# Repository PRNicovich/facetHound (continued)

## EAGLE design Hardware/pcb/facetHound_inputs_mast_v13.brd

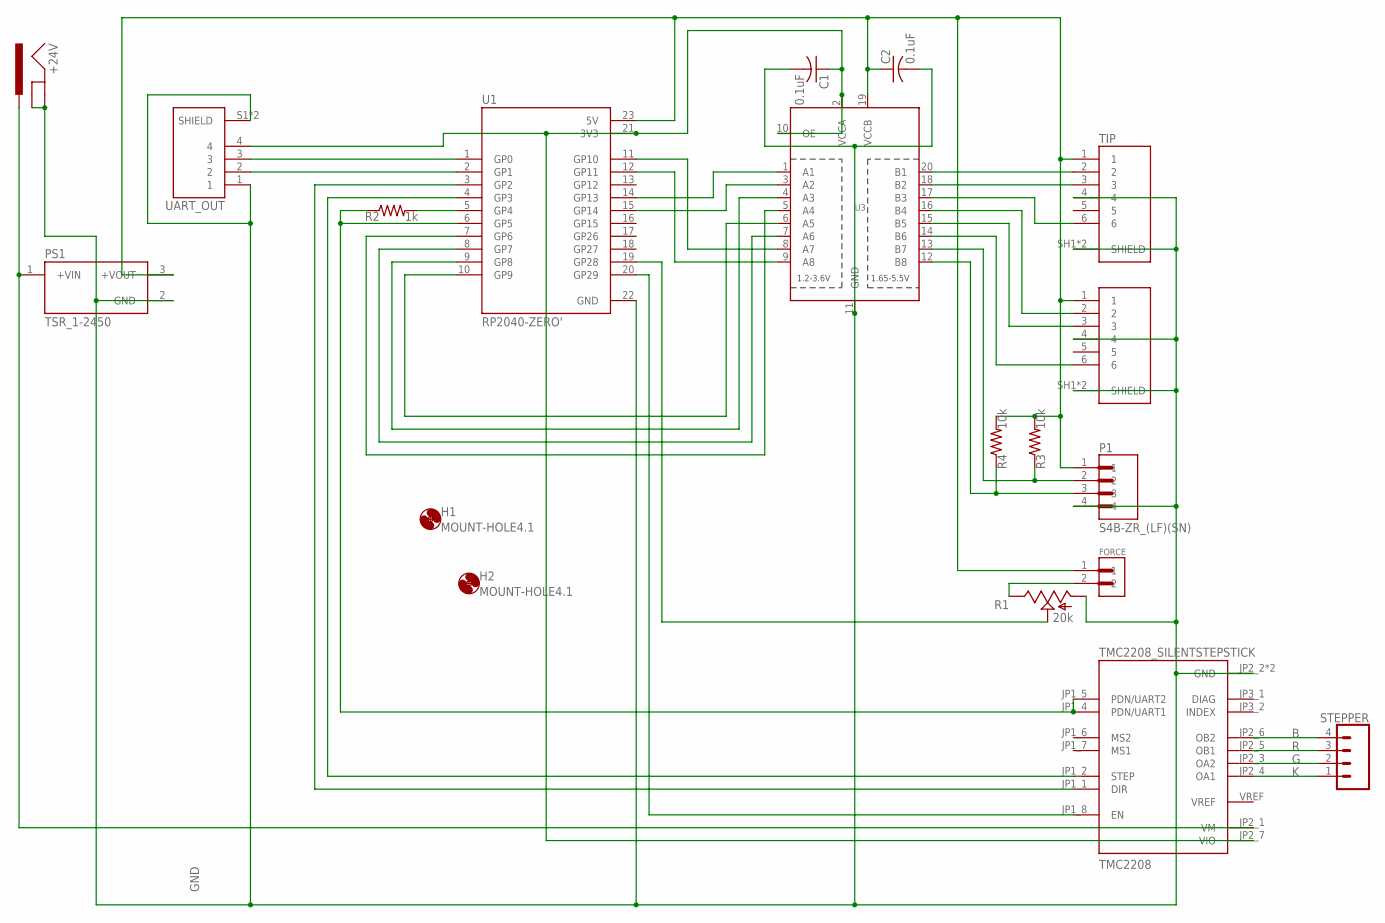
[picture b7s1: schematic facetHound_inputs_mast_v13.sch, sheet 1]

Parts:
+24V: POWER_JACKPOWER_JACK_SLOT; POWER_JACK_PTH_SLOT
C1, C2: 0.1uF; C1206
FORCE: S2B-ZR-SM4A-TF; JST_S2B-ZR-SM4A-TF
H1, H2: MOUNT-HOLE4.1; 4,1
P1: S4B-ZR_(LF)(SN); JST_S4B-ZR(LF)(SN)
PS1: TSR_1-2450; CONV_TSR_1-2450
R1: 20k; RJ9W
R2: 1k; R1206
R3, R4: 10k; R1206
STEPPER: CONN_04JST-PTH; JST-4-PTH
TILT: S6B-ZR-SM4A-TF(LF)(SN); JST_S6B-ZR-SM4A-TF(LF)(SN)
TIP: S6B-ZR-SM4A-TF(LF)(SN); JST_S6B-ZR-SM4A-TF(LF)(SN)
TMC2208: TMC2208_SILENTSTEPSTICK; MODULE_TMC2208_SILENTSTEPSTICK
U1: RP2040-ZERO'; MODULE_RP2040-ZERO
U3: TXB0108PWR; TSSOP20
UART_OUT: S4B-ZR-SM4A-TF(LF)(SN); JST_S4B-ZR-SM4A-TF(LF)(SN)

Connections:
B: STEPPER.4, TMC2208.JP2_6 (OB2)
G: STEPPER.2, TMC2208.JP2_3 (OA2)
GND: +24V.GND, +24V.GNDBREAK, C1.2, C2.2, P1.4, PS1.2 (GND), R1.A, TILT.4, TILT.SH1 (SHIELD), TILT.SH2 (SHIELD), TIP.4, TIP.SH1 (SHIELD), TIP.SH2 (SHIELD), TMC2208.JP2_2 (GND), TMC2208.JP2_8 (GND), U1.22 (GND), U3.11 (GND), UART_OUT.1, UART_OUT.S1 (SHIELD), UART_OUT.S2 (SHIELD)
K: STEPPER.1, TMC2208.JP2_4 (OA1)
unnamed: R2.1, TMC2208.JP1_4 (PDN/UART1), TMC2208.JP1_5 (PDN/UART2), U1.6 (GP5)
unnamed: C1.1, TMC2208.JP2_7 (VIO), U1.21 (3V3), U3.2 (VCCA), U3.10 (OE), UART_OUT.4
unnamed: R2.2, U1.5 (GP4)
unnamed: TMC2208.JP1_2 (STEP), U1.4 (GP3)
unnamed: TMC2208.JP1_1 (DIR), U1.3 (GP2)
unnamed: C2.1, FORCE.1, P1.1, PS1.3 (+VOUT), R3.2, R4.2, TILT.1, TIP.1, U1.23 (5V), U3.19 (VCCB)
unnamed: R1.S, U1.19 (GP28)
unnamed: TIP.2, U3.20 (B1)
unnamed: U1.2 (GP1), UART_OUT.2
unnamed: U1.1 (GP0), UART_OUT.3
unnamed: TIP.3, U3.18 (B2)
unnamed: TIP.6, U3.17 (B3)
unnamed: TILT.2, U3.16 (B4)
unnamed: TILT.3, U3.15 (B5)
unnamed: TILT.6, U3.14 (B6)
unnamed: P1.2, R3.1, U3.13 (B7)
unnamed: P1.3, R4.1, U3.12 (B8)
unnamed: TMC2208.JP1_8 (EN), U1.20 (GP29)
unnamed: +24V.PWR, PS1.1 (+VIN), TMC2208.JP2_1 (VM)
unnamed: U1.14 (GP13), U3.1 (A1)
unnamed: FORCE.2, R1.E
unnamed: U1.15 (GP14), U3.3 (A2)
unnamed: U1.9 (GP8), U3.4 (A3)
unnamed: U1.7 (GP6), U3.5 (A4)
unnamed: U1.10 (GP9), U3.6 (A5)
unnamed: U1.8 (GP7), U3.7 (A6)
unnamed: U1.12 (GP11), U3.9 (A8)
unnamed: U1.11 (GP10), U3.8 (A7)
R: STEPPER.3, TMC2208.JP2_5 (OB1)

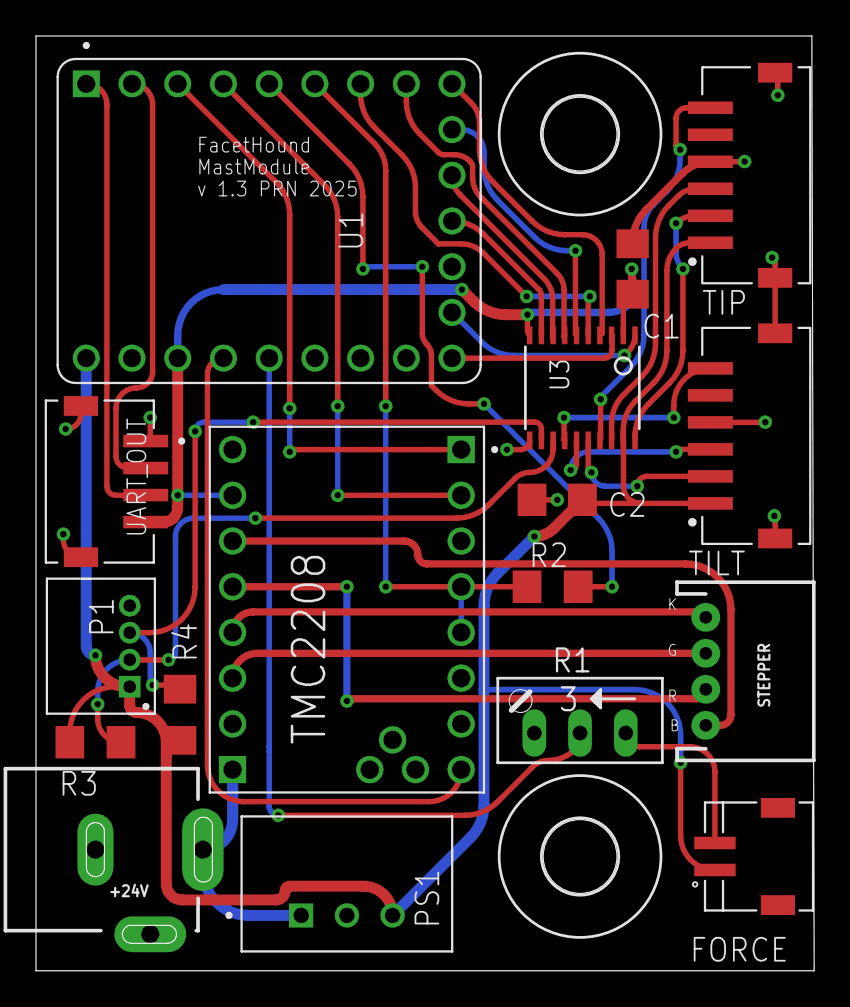
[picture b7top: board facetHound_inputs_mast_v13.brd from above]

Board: 2 copper layers, 43.2 x 51.9 mm, 19 parts (0 on the bottom side), 33 nets.

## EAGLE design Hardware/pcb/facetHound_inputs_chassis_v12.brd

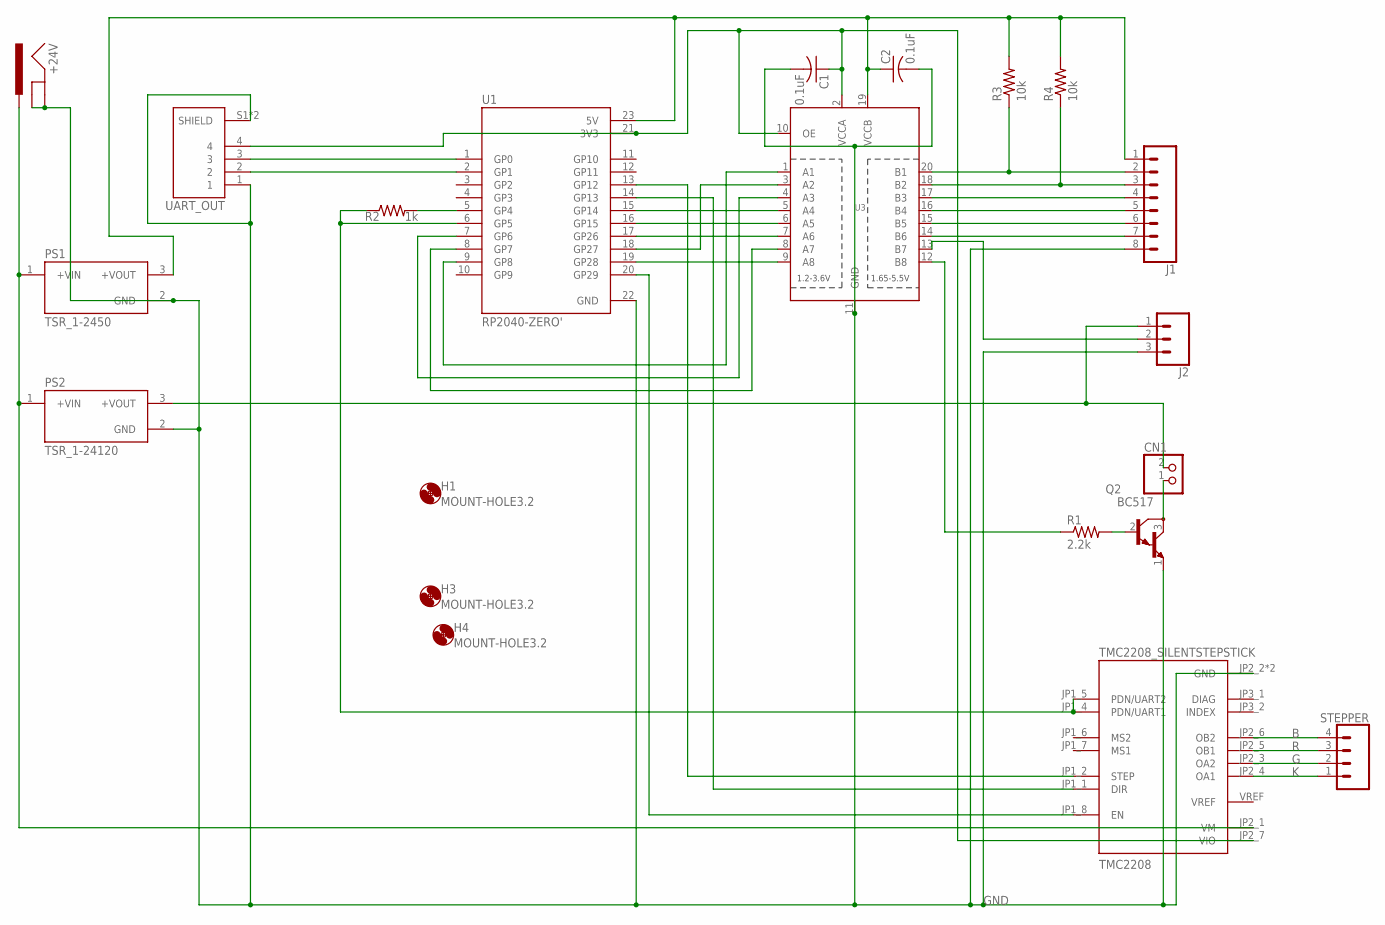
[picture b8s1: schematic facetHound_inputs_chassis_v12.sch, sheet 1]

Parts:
+24V: POWER_JACKPOWER_JACK_SLOT; POWER_JACK_PTH_SLOT
C1, C2: 0.1uF; C1206
CN1: JST_2PIN-THM-RA; JST-PH-2-THM-RA
H1, H3, H4: MOUNT-HOLE3.2; 3,2
J1: CONN_08LONGPADS; 1X08_LONGPADS
J2: CONN_03SCREW; SCREWTERMINAL-3.5MM-3
PS1: TSR_1-2450; CONV_TSR_1-2450
PS2: TSR_1-24120; CONV_TSR_1-2450
Q2: BC517; TO92
R1: 2.2k; M1206
R2: 1k; R1206
R3, R4: 10k; M1206
STEPPER: CONN_04JST-PTH; JST-4-PTH
TMC2208: TMC2208_SILENTSTEPSTICK; MODULE_TMC2208_SILENTSTEPSTICK
U1: RP2040-ZERO'; MODULE_RP2040-ZERO
U3: TXB0108PWR; TSSOP20
UART_OUT: S4B-ZR-SM4A-TF(LF)(SN); JST_S4B-ZR-SM4A-TF(LF)(SN)

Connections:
B: STEPPER.4, TMC2208.JP2_6 (OB2)
G: STEPPER.2, TMC2208.JP2_3 (OA2)
GND: +24V.GND, +24V.GNDBREAK, C1.2, C2.2, J1.8, J2.3, PS1.2 (GND), PS2.2 (GND), Q2.1 (E), TMC2208.JP2_2 (GND), TMC2208.JP2_8 (GND), U1.22 (GND), U3.11 (GND), UART_OUT.1, UART_OUT.S1 (SHIELD), UART_OUT.S2 (SHIELD)
K: STEPPER.1, TMC2208.JP2_4 (OA1)
unnamed: R2.1, TMC2208.JP1_4 (PDN/UART1), TMC2208.JP1_5 (PDN/UART2), U1.6 (GP5)
unnamed: R2.2, U1.5 (GP4)
unnamed: C1.1, TMC2208.JP2_7 (VIO), U1.21 (3V3), U3.2 (VCCA), U3.10 (OE), UART_OUT.4
unnamed: TMC2208.JP1_1 (DIR), U1.14 (GP13)
unnamed: TMC2208.JP1_2 (STEP), U1.13 (GP12)
unnamed: R1.1, U3.12 (B8)
unnamed: Q2.2 (B), R1.2
unnamed: C2.1, J1.1, PS1.3 (+VOUT), R3.2, R4.2, U1.23 (5V), U3.19 (VCCB)
unnamed: U1.2 (GP1), UART_OUT.2
unnamed: U1.1 (GP0), UART_OUT.3
unnamed: CN1.2 (1), J2.1, PS2.3 (+VOUT)
unnamed: J1.2, R3.1, U3.20 (B1)
unnamed: J1.3, R4.1, U3.18 (B2)
unnamed: J1.4, U3.17 (B3)
unnamed: J1.5, U3.16 (B4)
unnamed: J1.6, U3.15 (B5)
unnamed: J1.7, U3.14 (B6)
unnamed: TMC2208.JP1_8 (EN), U1.20 (GP29)
unnamed: +24V.PWR, PS1.1 (+VIN), PS2.1 (+VIN), TMC2208.JP2_1 (VM)
unnamed: J2.2, U3.13 (B7)
unnamed: U1.9 (GP8), U3.1 (A1)
unnamed: CN1.1 (2), Q2.3 (C)
unnamed: U1.18 (GP27), U3.3 (A2)
unnamed: U1.7 (GP6), U3.4 (A3)
unnamed: U1.15 (GP14), U3.5 (A4)
unnamed: U1.16 (GP15), U3.6 (A5)
unnamed: U1.17 (GP26), U3.7 (A6)
unnamed: U1.8 (GP7), U3.8 (A7)
unnamed: U1.19 (GP28), U3.9 (A8)
R: STEPPER.3, TMC2208.JP2_5 (OB1)

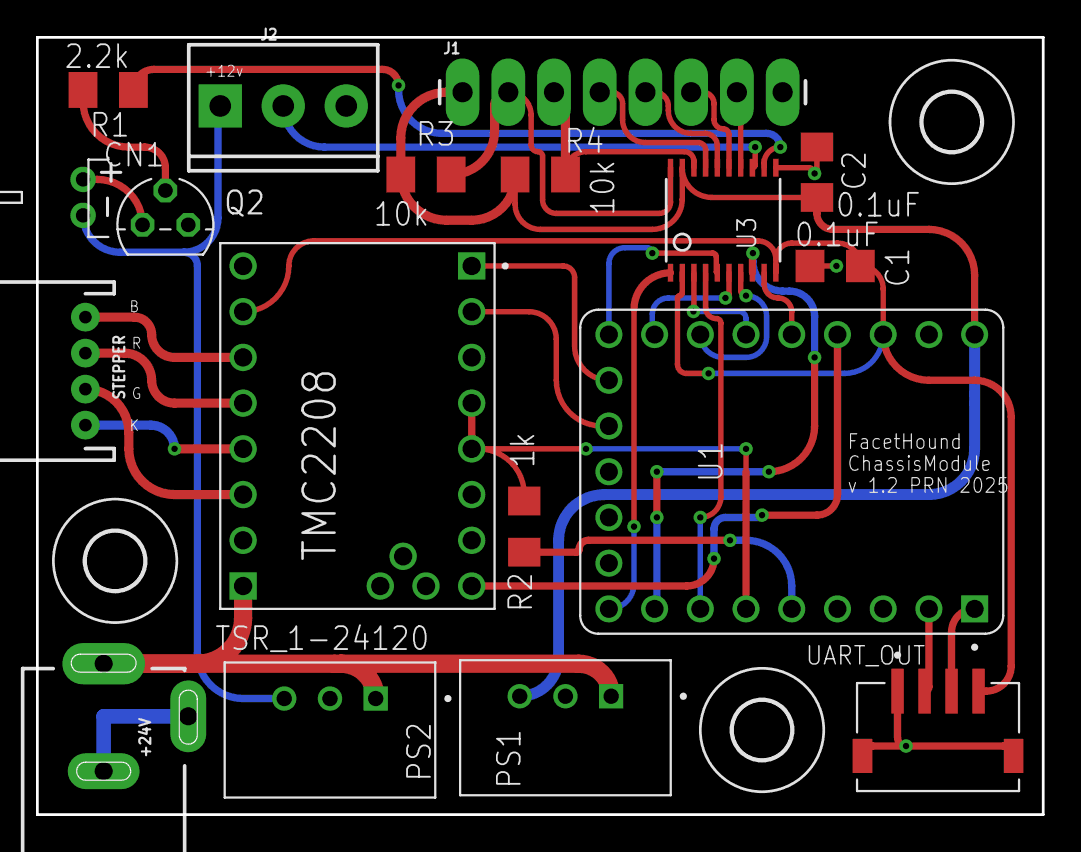
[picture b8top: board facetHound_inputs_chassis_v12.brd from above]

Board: 2 copper layers, 55.9 x 43.2 mm, 21 parts (0 on the bottom side), 34 nets.

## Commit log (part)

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2025-06-04 Adding in hardware files
2025-06-20 First round of post delivery edits.
2025-06-20 Reconciling source data
2025-07-08 Adding in templates and print aids.
2025-07-17 work
2025-07-17 more
2025-07-26 gem redering working
2025-08-16 Integration updates
2025-08-26 Mostly averaging and actually fixing it
2025-08-27 display module
2025-08-29 more coms fixes
2025-09-10 testing
2025-09-11 Create LICENSE
    add license file
2025-09-12 Add pdfs
2025-09-19 Bug fixes and readme
2025-09-29 80 index
2025-10-10 markPoints
2025-10-11 Adding TFT setup file
2025-10-12 Servo mode, mark points, wheel index select
2025-10-31 Checksum between base and display
2025-10-31 Fix bug preventing negative tip angles
2026-05-28 updates to v8 hardware
